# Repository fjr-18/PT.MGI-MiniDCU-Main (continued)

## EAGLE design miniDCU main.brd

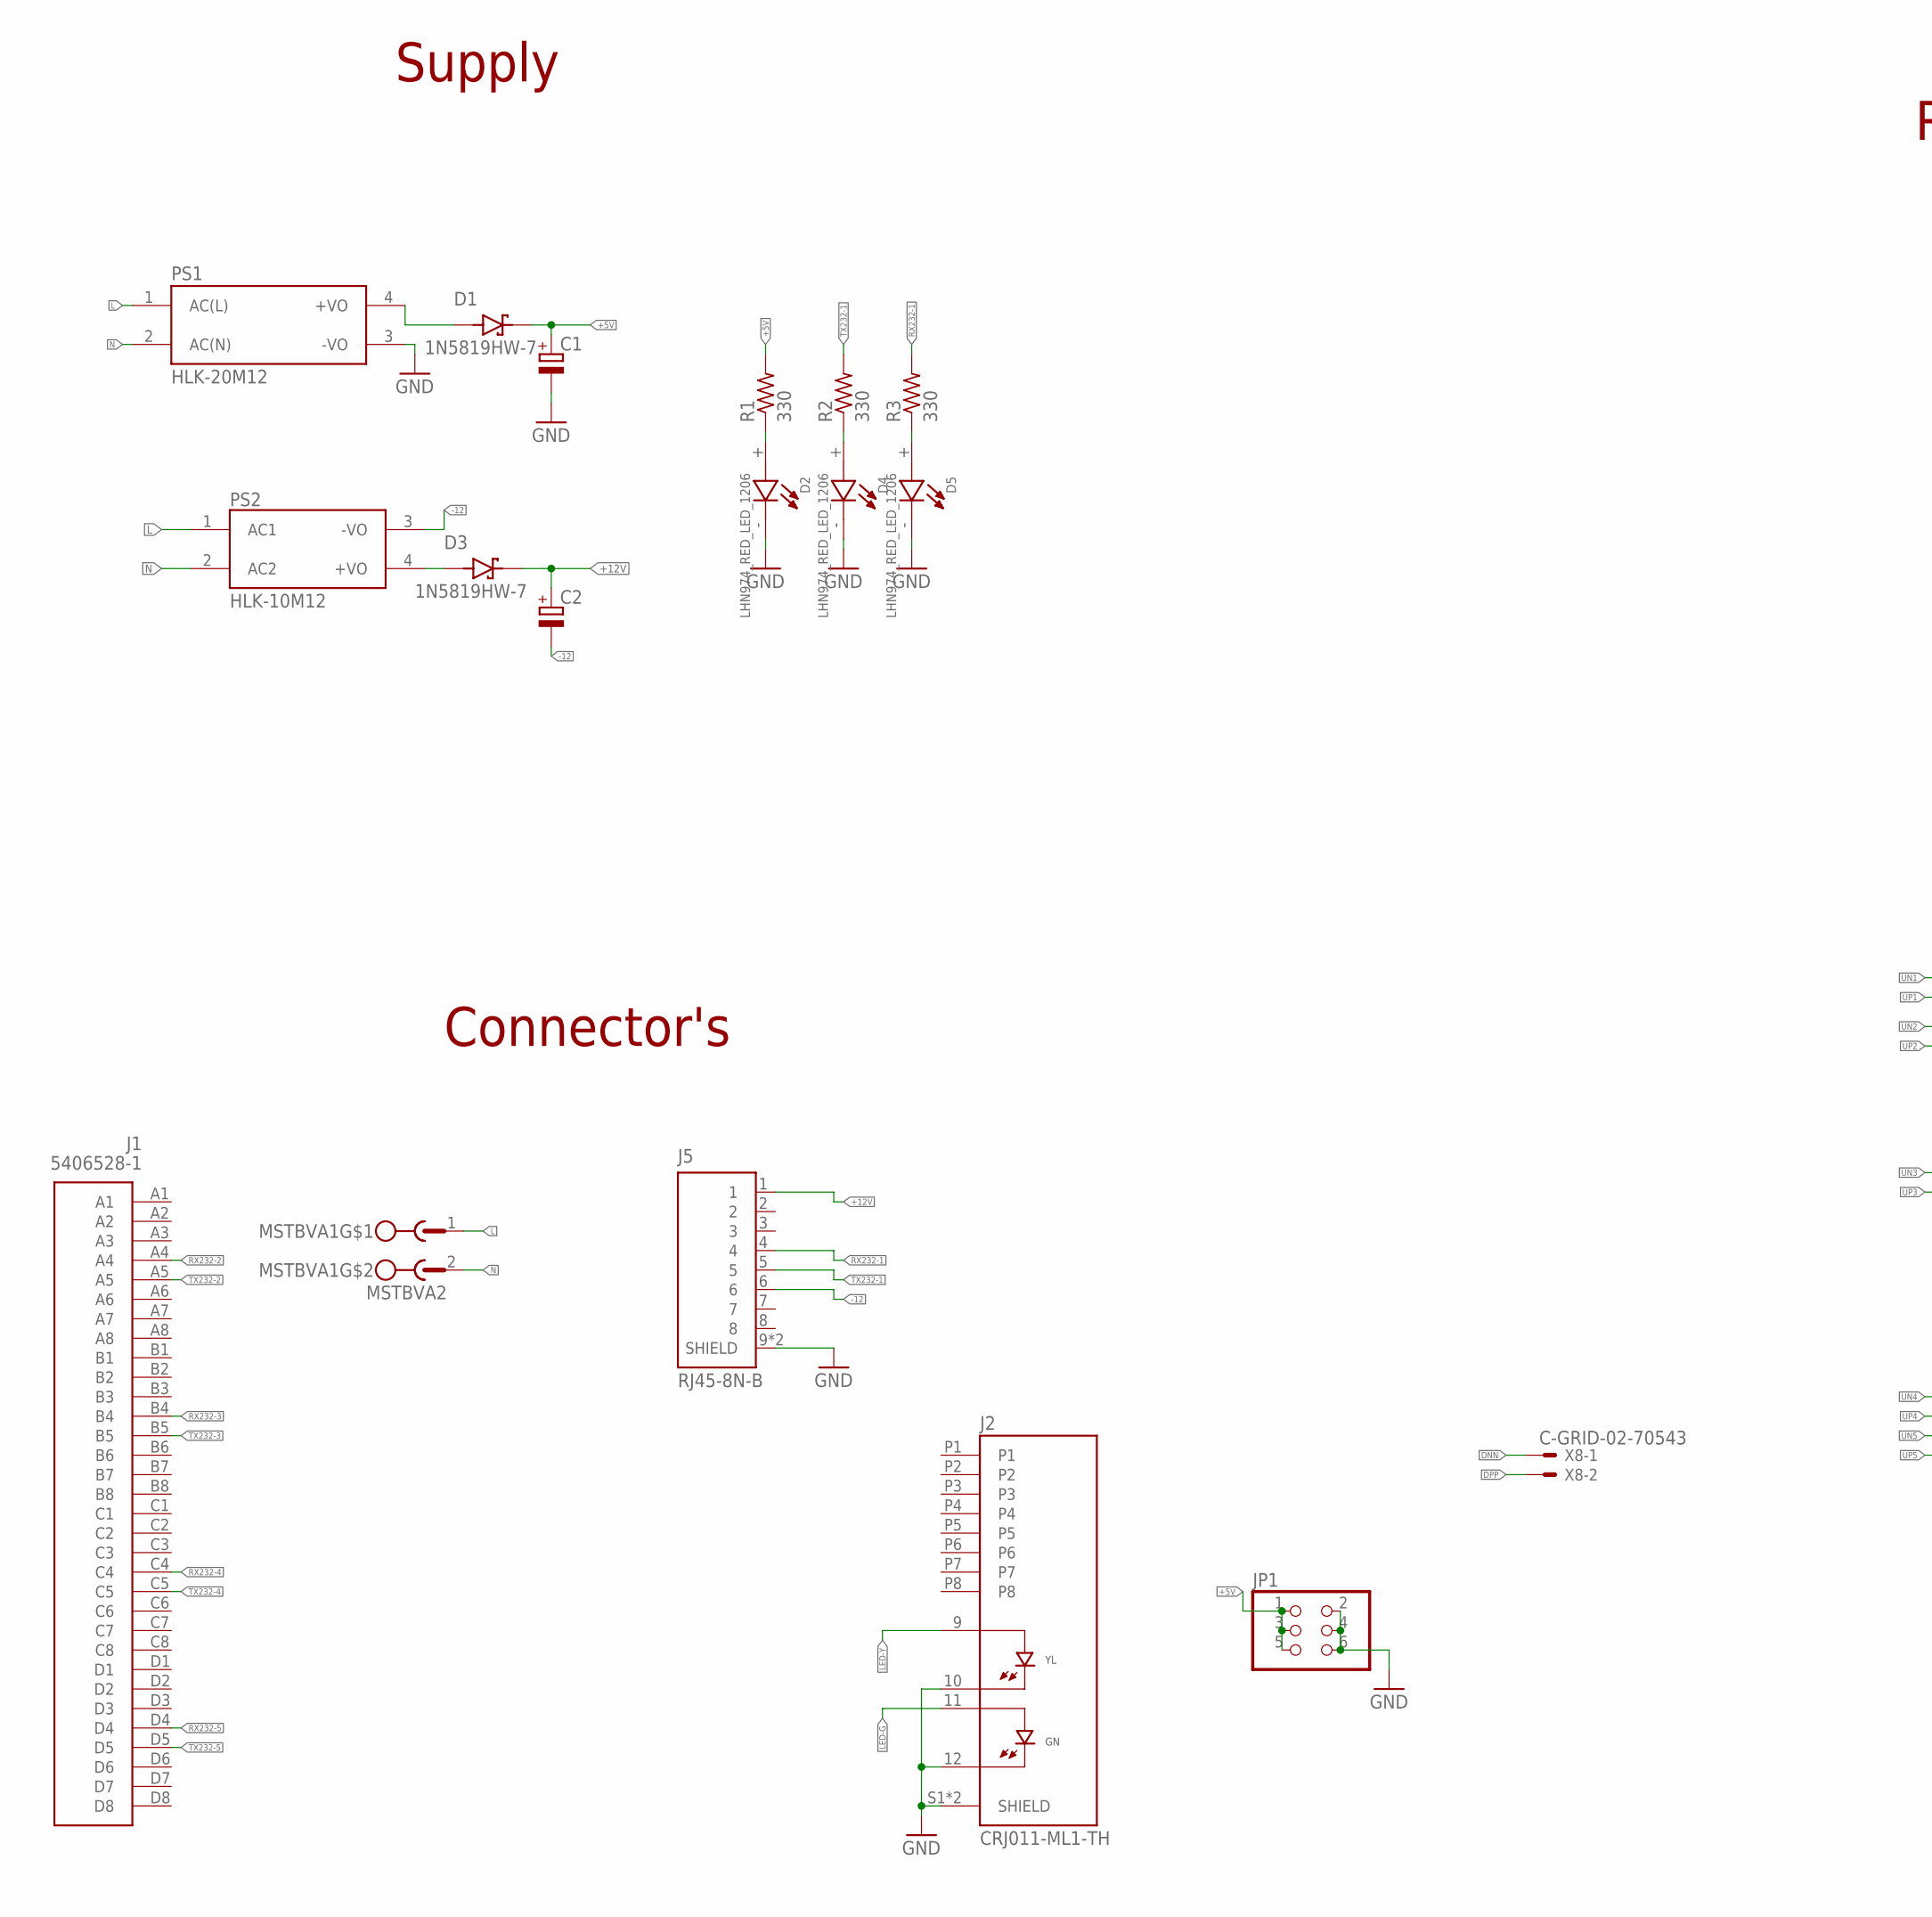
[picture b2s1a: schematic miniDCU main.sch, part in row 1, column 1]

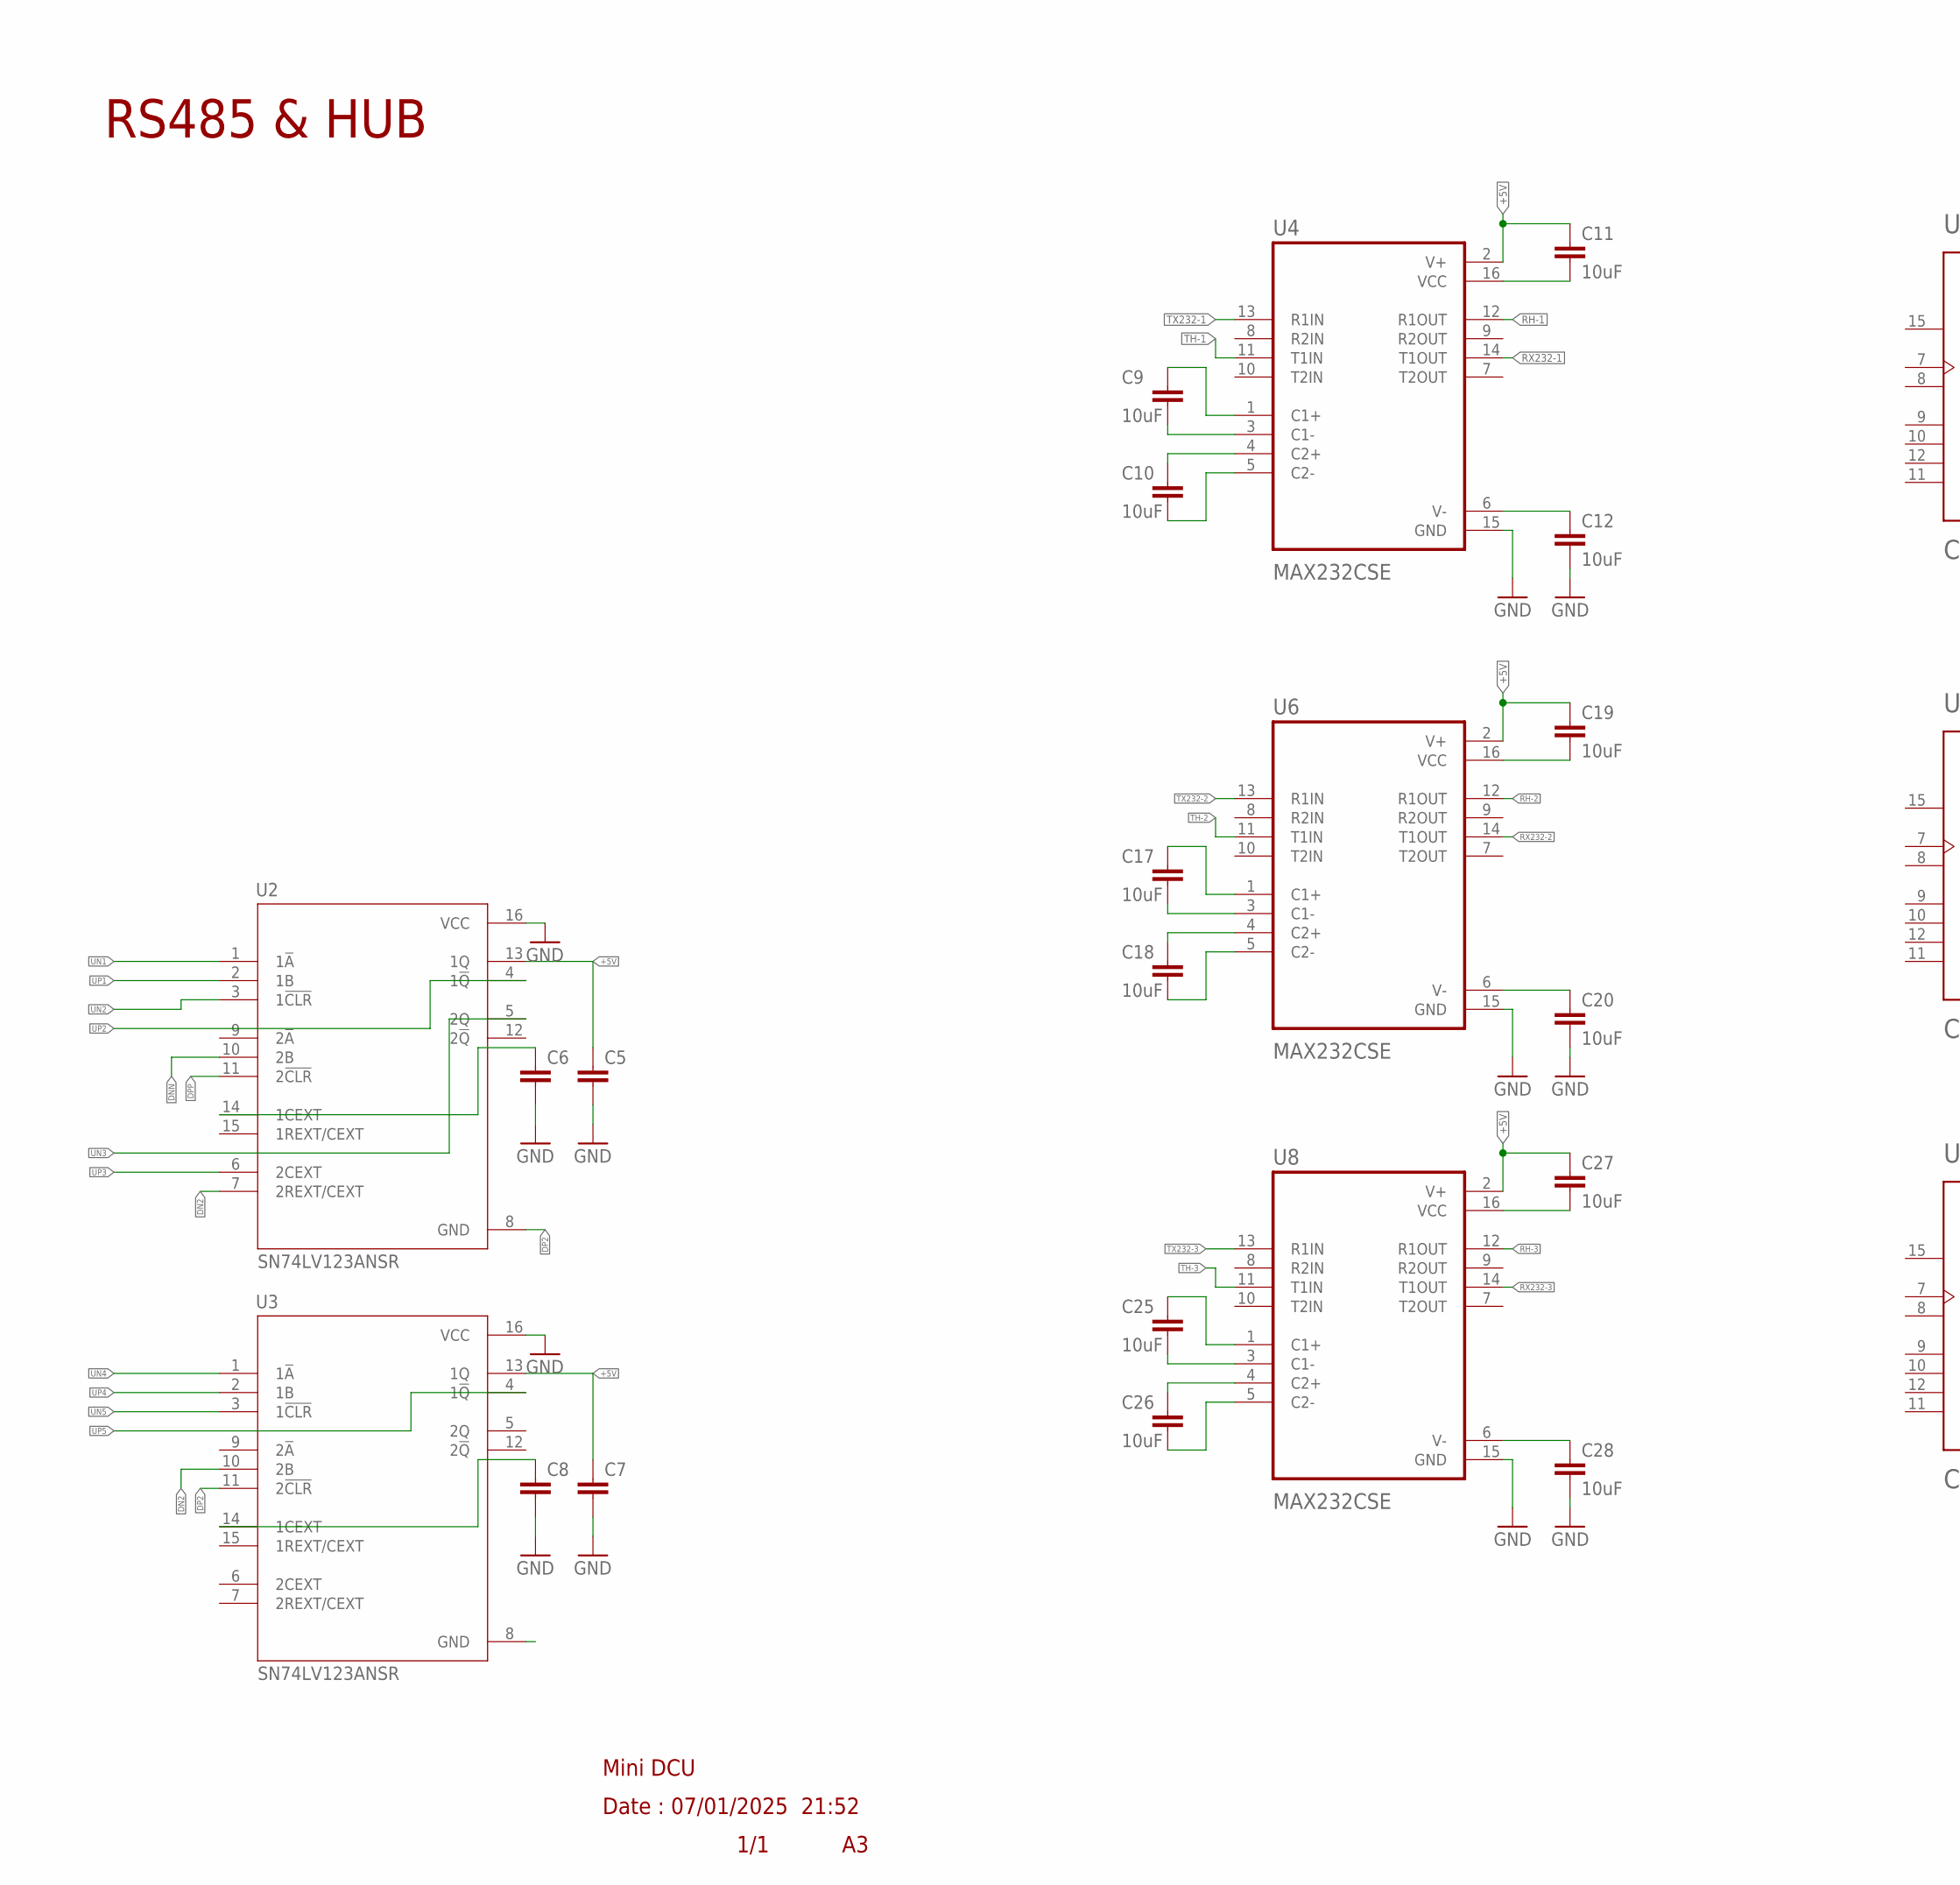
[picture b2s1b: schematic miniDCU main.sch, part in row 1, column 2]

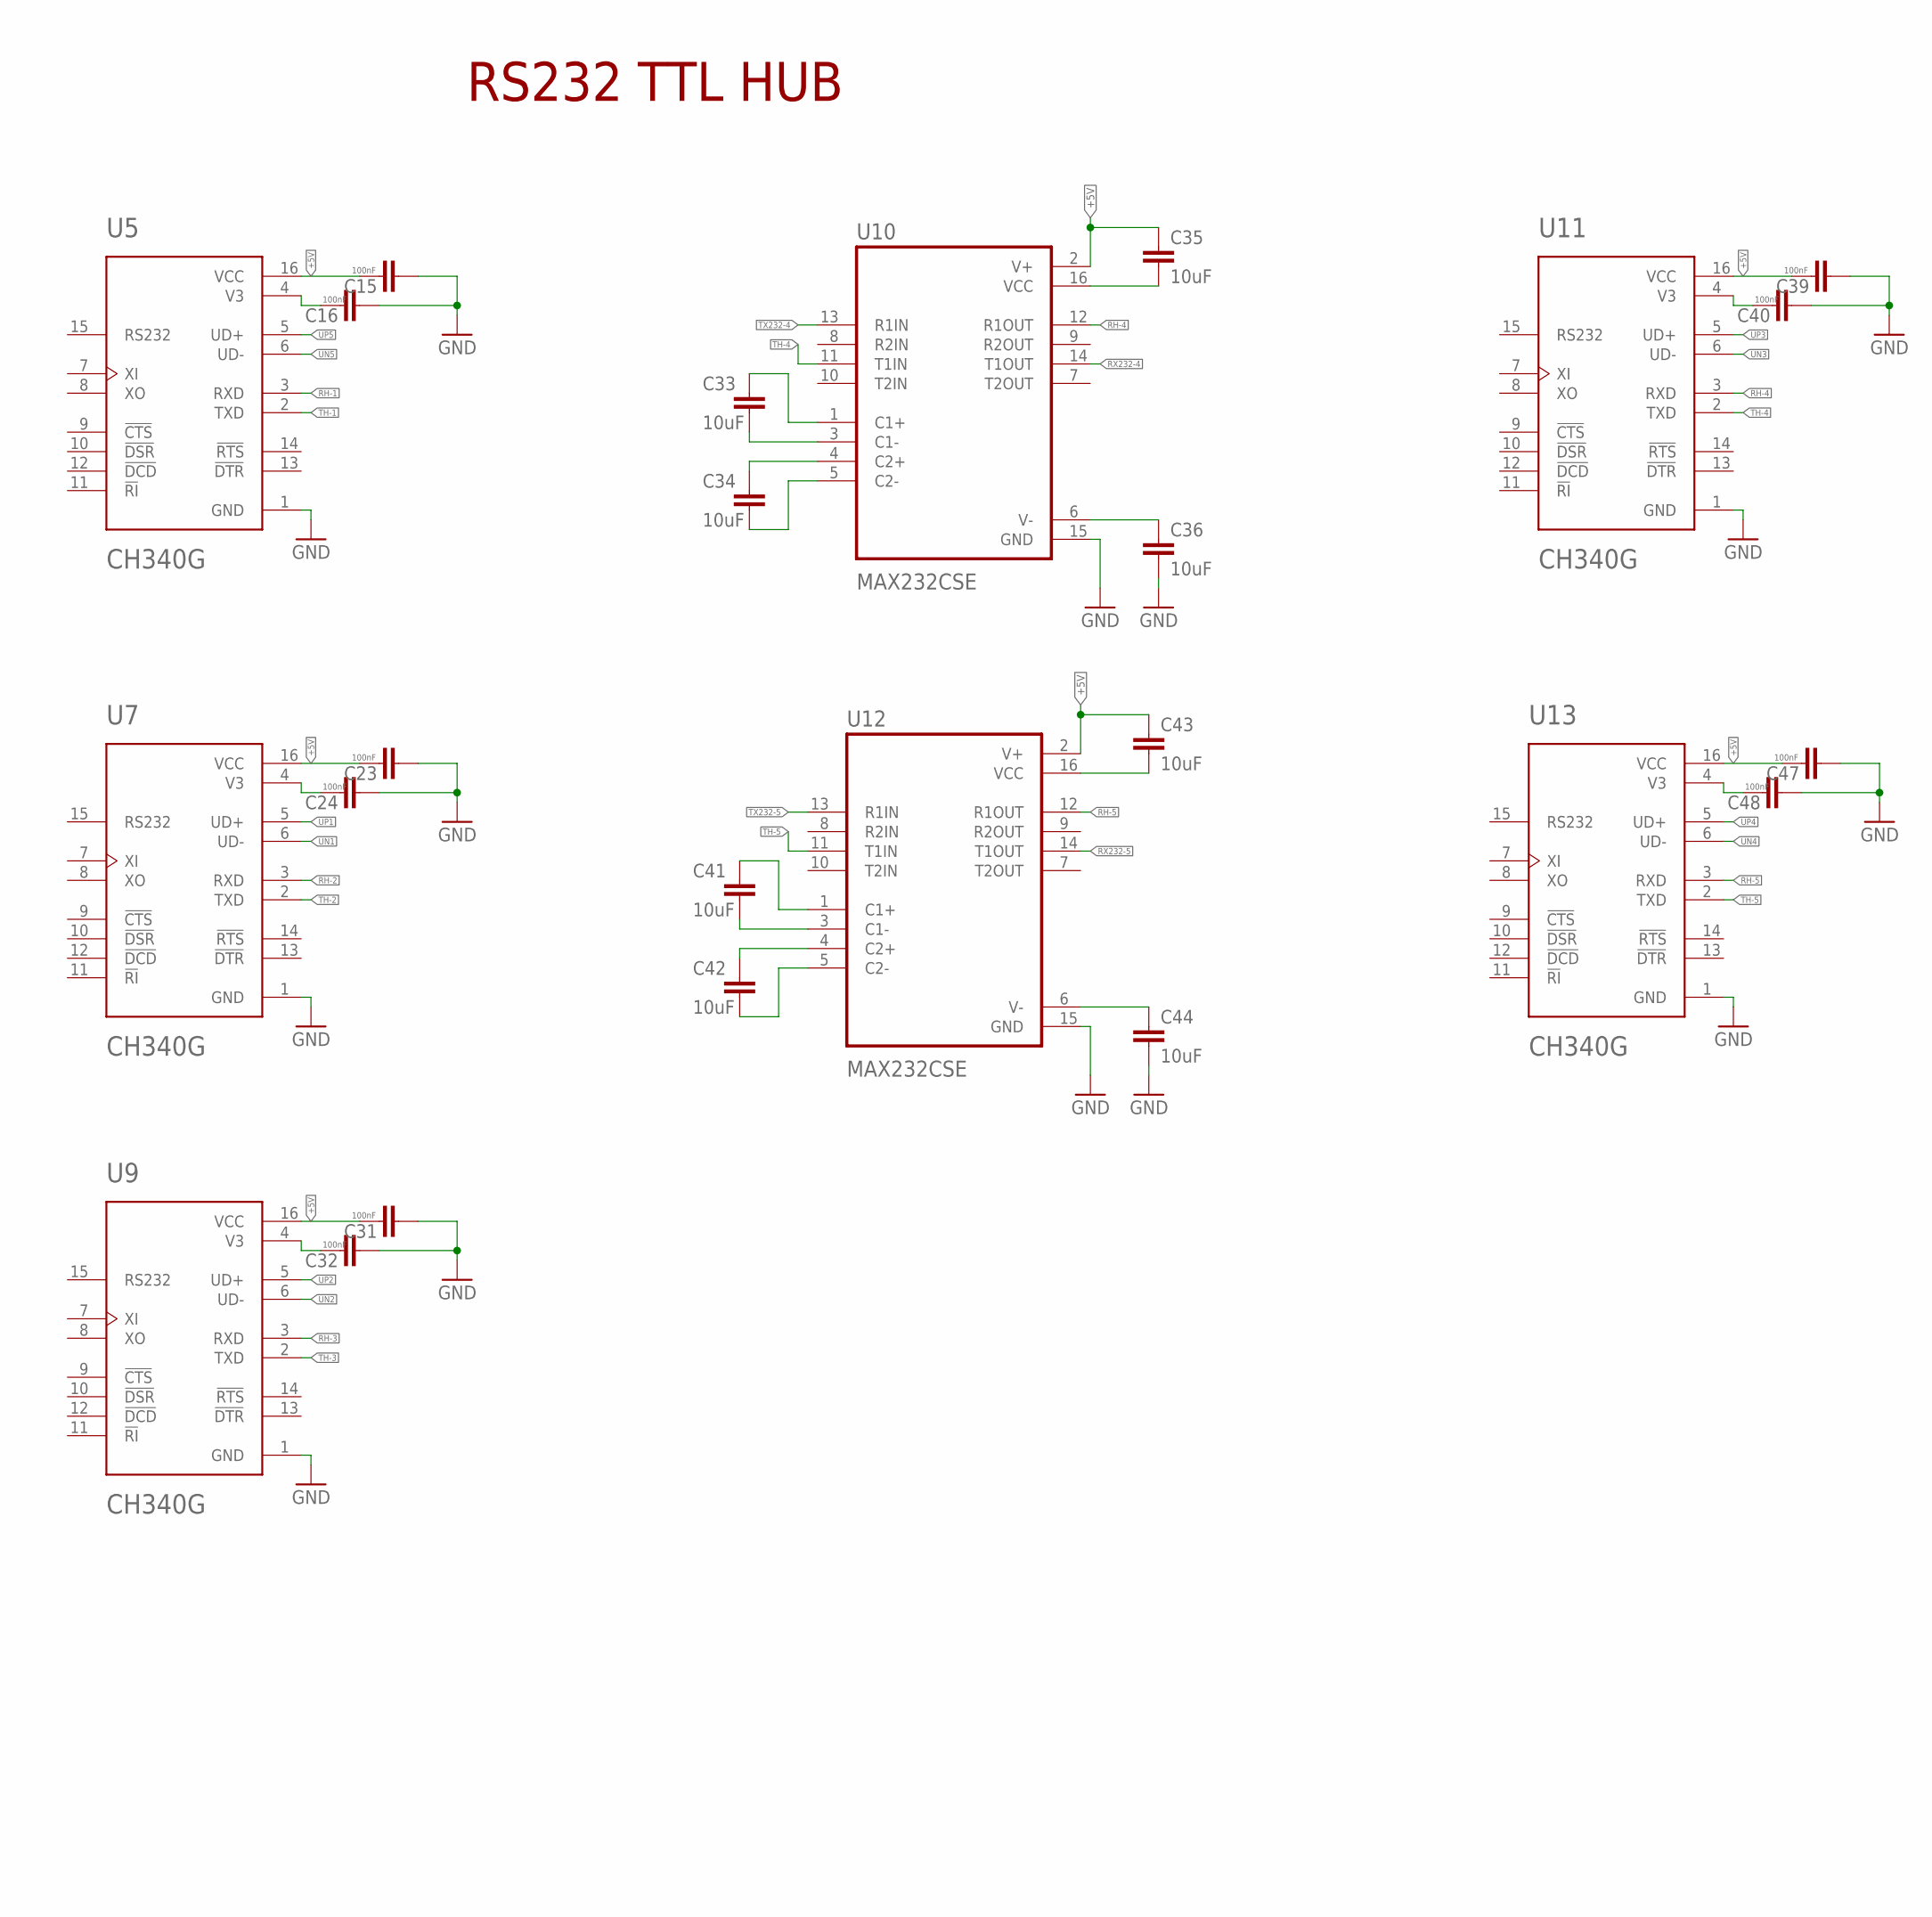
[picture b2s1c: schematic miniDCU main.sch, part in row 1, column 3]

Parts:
C1, C2: CPOL-EU153CLV-0505; 153CLV-0505
C5, C6, C7, C8: C-EUC0603K; C0603K
C9, C10, C11, C12, C17, C18, C19, C20, C25, C26, C27, C28, C33, C34, C35, C36, C41, C42, C43, C44: 10uF; C0805
C15, C16, C23, C24, C31, C32, C39, C40, C47, C48: 100nF; C0805K
D1, D3: 1N5819HW-7; SOD3715X145N
D2, D4, D5: LHN974_RED_LED_1206; LEDC3216X120N
J1: 5406528-1
J2: CRJ011-ML1-TH; CUI_CRJ011-ML1-TH
J5: RJ45-8N-B; TE_RJ45-8N-B
JP1: PINHD-2X3; 2X03
MSTBVA1: MSTBVA2
PS1: HLK-20M12; CONV_HLK-20M12
PS2: HLK-10M12; CONV_HLK-10M12
R1, R2, R3: 330; M0805
U2, U3: SN74LV123ANSR; SOIC127P780X200-16N
U4, U6, U8, U10, U12: MAX232CSE; SOIC127P600X175-16N
U5, U7, U9, U11, U13: CH340G; SOIC127P600X180-16N
X8: C-GRID-02-70543; 70543-02

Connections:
+5V: C1.+, C5.1, C7.1, C11.1, C15.1, C19.1, C23.1, C27.1, C31.1, C35.1, C39.1, C43.1, C47.1, D1.C (K), JP1.1, JP1.3, JP1.5, R1.2, U2.13 (1Q), U3.13 (1Q), U4.2 (V+), U5.16 (VCC), U6.2 (V+), U7.16 (VCC), U8.2 (V+), U9.16 (VCC), U10.2 (V+), U11.16 (VCC), U12.2 (V+), U13.16 (VCC)
+12V: C2.+, D3.C (K), J5.1
-12: C2.-, J5.6, PS2.3 (-VO)
DN2: U2.7 (2REXT/CEXT), U3.10 (2B)
DNN: U2.10 (2B), X8.1
DP2: U2.8 (GND), U3.11 (2!CLR)
DPP: U2.11 (2!CLR), X8.2
GND: C1.-, C5.2, C6.2, C7.2, C8.2, C12.2, C15.2, C16.2, C20.2, C23.2, C24.2, C28.2, C31.2, C32.2, C36.2, C39.2, C40.2, C44.2, C47.2, C48.2, D2.-, D4.-, D5.-, J2.10, J2.12, J2.S1 (SHIELD), J2.S2 (SHIELD), J5.9 (SHIELD), J5.10 (SHIELD), JP1.2, JP1.4, JP1.6, PS1.3 (-VO), U2.16 (VCC), U3.16 (VCC), U4.15 (GND), U5.1 (GND), U6.15 (GND), U7.1 (GND), U8.15 (GND), U9.1 (GND), U10.15 (GND), U11.1 (GND), U12.15 (GND), U13.1 (GND)
L: MSTBVA1.1, PS1.1 (AC(L)), PS2.1 (AC1)
LED-G: J2.11
LED-Y: J2.9
N: MSTBVA1.2, PS1.2 (AC(N)), PS2.2 (AC2)
unnamed: D1.A, PS1.4 (+VO)
unnamed: D4.+, R2.1
unnamed: D2.+, R1.1
unnamed: D5.+, R3.1
unnamed: D3.A, PS2.4 (+VO)
unnamed: C9.2, U4.3 (C1-)
unnamed: C9.1, U4.1 (C1+)
unnamed: C10.1, U4.4 (C2+)
unnamed: C10.2, U4.5 (C2-)
unnamed: C11.2, U4.16 (VCC)
unnamed: C12.1, U4.6 (V-)
unnamed: C16.1, U5.4 (V3)
unnamed: C17.2, U6.3 (C1-)
unnamed: C17.1, U6.1 (C1+)
unnamed: C18.1, U6.4 (C2+)
unnamed: C18.2, U6.5 (C2-)
unnamed: C19.2, U6.16 (VCC)
unnamed: C20.1, U6.6 (V-)
unnamed: C24.1, U7.4 (V3)
unnamed: C25.2, U8.3 (C1-)
unnamed: C25.1, U8.1 (C1+)
unnamed: C26.1, U8.4 (C2+)
unnamed: C26.2, U8.5 (C2-)
unnamed: C27.2, U8.16 (VCC)
unnamed: C28.1, U8.6 (V-)
unnamed: C32.1, U9.4 (V3)
unnamed: C33.2, U10.3 (C1-)
unnamed: C33.1, U10.1 (C1+)
unnamed: C34.1, U10.4 (C2+)
unnamed: C8.1, U3.14 (1CEXT)
unnamed: C34.2, U10.5 (C2-)
unnamed: C35.2, U10.16 (VCC)
unnamed: C36.1, U10.6 (V-)
unnamed: C6.1, U2.14 (1CEXT)
unnamed: C40.1, U11.4 (V3)
unnamed: C41.2, U12.3 (C1-)
unnamed: C41.1, U12.1 (C1+)
unnamed: C42.1, U12.4 (C2+)
unnamed: C42.2, U12.5 (C2-)
unnamed: C43.2, U12.16 (VCC)
unnamed: C44.1, U12.6 (V-)
unnamed: C48.1, U13.4 (V3)
RH-1: U4.12 (R1OUT), U5.3 (RXD)
RH-2: U6.12 (R1OUT), U7.3 (RXD)
RH-3: U8.12 (R1OUT), U9.3 (RXD)
RH-4: U10.12 (R1OUT), U11.3 (RXD)
RH-5: U12.12 (R1OUT), U13.3 (RXD)
RX232-1: J5.4, R3.2, U4.14 (T1OUT)
RX232-2: J1.A4, U6.14 (T1OUT)
RX232-3: J1.B4, U8.14 (T1OUT)
RX232-4: J1.C4, U10.14 (T1OUT)
RX232-5: J1.D4, U12.14 (T1OUT)
TH-1: U4.11 (T1IN), U5.2 (TXD)
TH-2: U6.11 (T1IN), U7.2 (TXD)
TH-3: U8.11 (T1IN), U9.2 (TXD)
TH-4: U10.11 (T1IN), U11.2 (TXD)
TH-5: U12.11 (T1IN), U13.2 (TXD)
TX232-1: J5.5, R2.2, U4.13 (R1IN)
TX232-2: J1.A5, U6.13 (R1IN)
TX232-3: J1.B5, U8.13 (R1IN)
TX232-4: J1.C5, U10.13 (R1IN)
TX232-5: J1.D5, U12.13 (R1IN)
UN1: U2.1 (1!A), U7.6 (UD-)
UN2: U2.3 (1!CLR), U9.6 (UD-)
UN3: U2.5 (2Q), U11.6 (UD-)
UN4: U3.1 (1!A), U13.6 (UD-)
UN5: U3.3 (1!CLR), U5.6 (UD-)
UP1: U2.2 (1B), U7.5 (UD+)
UP2: U2.4 (1!Q), U9.5 (UD+)
UP3: U2.6 (2CEXT), U11.5 (UD+)
UP4: U3.2 (1B), U13.5 (UD+)
UP5: U3.4 (1!Q), U5.5 (UD+)

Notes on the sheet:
Mini DCU
Date : 07/01/2025 21:52
1/1
Supply
Connector's
RS485 & HUB
RS232 TTL HUB

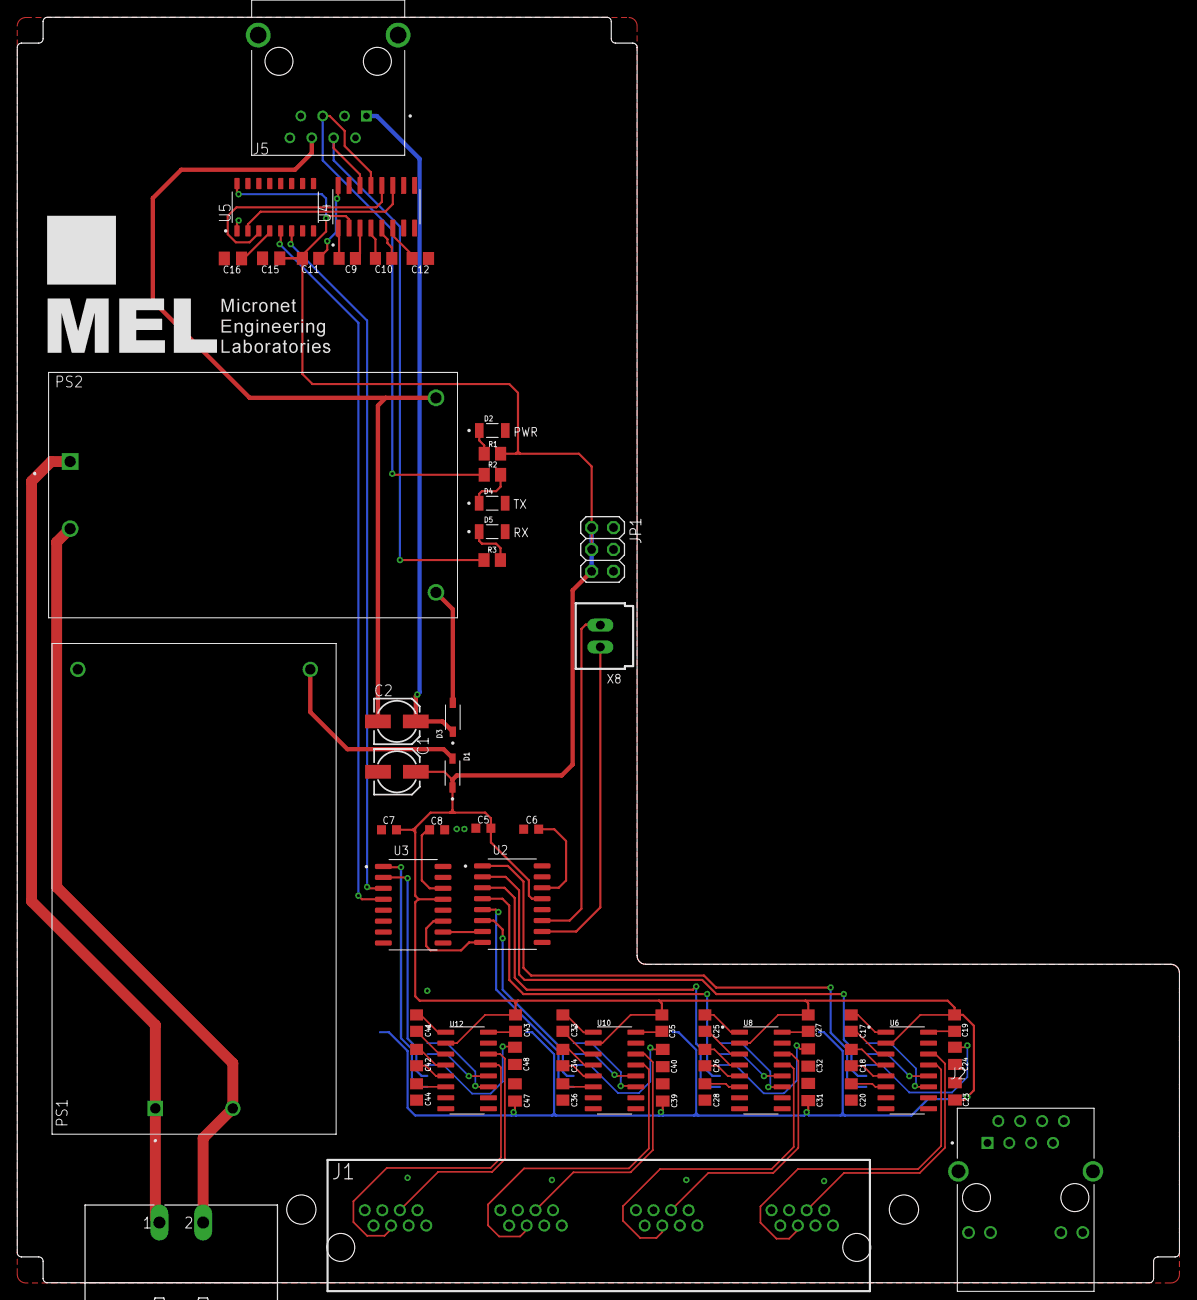
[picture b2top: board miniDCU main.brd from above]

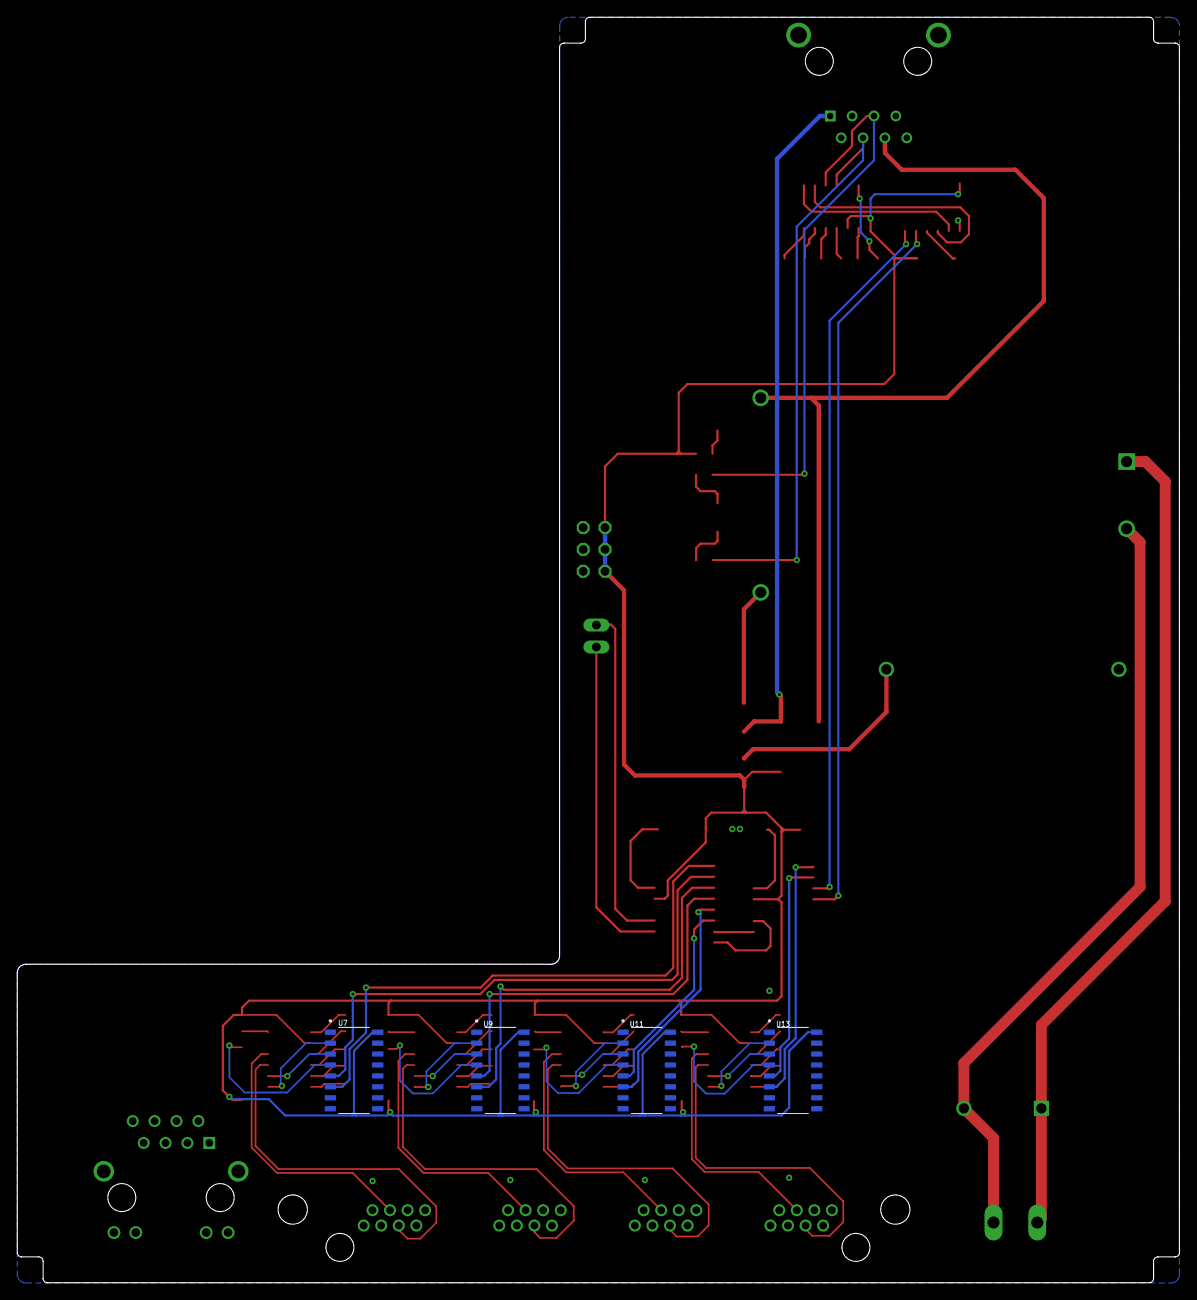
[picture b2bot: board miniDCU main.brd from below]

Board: 2 copper layers, 135.0 x 147.0 mm, 64 parts (4 on the bottom side), 82 nets.
